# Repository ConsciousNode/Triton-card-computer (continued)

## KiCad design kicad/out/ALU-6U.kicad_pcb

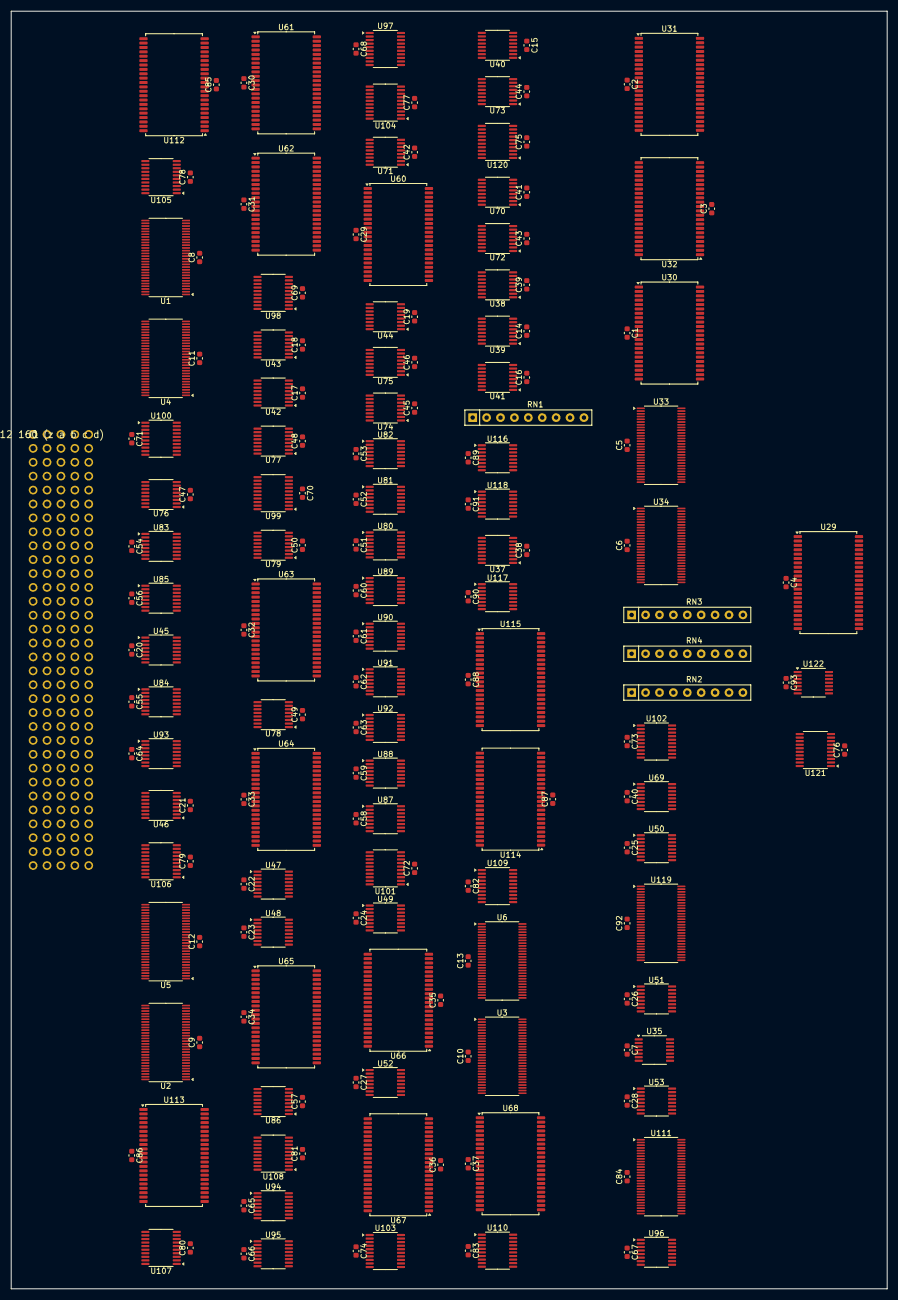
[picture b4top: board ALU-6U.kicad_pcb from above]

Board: 4 copper layers, 160.0 x 233.3 mm, 191 parts (0 on the bottom side), 470 nets, no tracks yet.

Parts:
C1, C2, C3, C4, C5, C6, C7, C8, C9, C10, C11, C12, C13, C14, C15, C16, C17, C18, C19, C20, C21, C22, C23, C24, C25, C26, C27, C28, C29, C30, C31, C32, C33, C34, C35, C36, C37, C38, C39, C40, C41, C42, C43, C44, C45, C46, C47, C48, C49, C50, C51, C52, C53, C54, C55, C56, C57, C58, C59, C60, C61, C62, C63, C64, C65, C66, C67, C68, C69, C70, C71, C72, C73, C74, C75, C76, C77, C78, C79, C80, C81, C82, C83, C84, C85, C86, C87, C88, C89, C90, C91, C92, C93: 100n; C_0603_1608Metric
J1: DIN41612 160 (z a b c d)
RN1, RN2, RN3, RN4: RPACK8; R_Array_SIP9
U1, U2, U3, U4, U5, U6, U33, U34, U111, U119: ALVCH16823; TSSOP-56_6.1x14mm_P0.5mm
U29, U30, U31, U32, U60, U61, U62, U63, U64, U65, U66, U67, U68, U112, U113, U114, U115: IS61WV5128; TSOP-II-44_10.16x18.41mm_P0.8mm
U35: LVC32; TSSOP-14_4.4x5mm_P0.65mm
U37, U39, U40, U69, U116, U117, U118: LVC153; TSSOP-16_4.4x5mm_P0.65mm
U38, U41, U42, U43, U44, U45, U46, U47, U48, U49, U50, U51, U52, U53: LVC157; TSSOP-16_4.4x5mm_P0.65mm
U70, U71, U72, U73, U74, U75, U76, U77, U78, U79, U80, U81, U82, U83, U84, U85, U86, U87, U88, U89, U90, U91, U92, U93, U94, U95, U96: CBTLV3253; TSSOP-16_4.4x5mm_P0.65mm
U97, U98, U99, U100, U101, U102, U103, U120, U121: CBTLV3245; TSSOP-20_4.4x6.5mm_P0.65mm
U104, U105, U106, U107, U108, U109, U110: LVC245; TSSOP-20_4.4x6.5mm_P0.65mm
U122: LVC04; TSSOP-14_4.4x5mm_P0.65mm

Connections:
+3V3: C1.1, C2.1, C3.1, C4.1, C5.1, C6.1, C7.1, C8.1, C9.1, C10.1, C11.1, C12.1, C13.1, C14.1, C15.1, C16.1, C17.1, C18.1, C19.1, C20.1, C21.1, C22.1, C23.1, C24.1, C25.1, C26.1, C27.1, C28.1, C29.1, C30.1, C31.1, C32.1, C33.1, C34.1, C35.1, C36.1, C37.1, C38.1, C39.1, C40.1, C41.1, C42.1, C43.1, C44.1, C45.1, C46.1, C47.1, C48.1, C49.1, C50.1, C51.1, C52.1, C53.1, C54.1, C55.1, C56.1, C57.1, C58.1, C59.1, C60.1, C61.1, C62.1, C63.1, C64.1, C65.1, C66.1, C67.1, C68.1, C69.1, C70.1, C71.1, C72.1, C73.1, C74.1, C75.1, C76.1, C77.1, C78.1, C79.1, C80.1, C81.1, C82.1, C83.1, C84.1, C85.1, C86.1, C87.1, C88.1, C89.1, C90.1, C91.1, C92.1, C93.1, J1.z2, J1.z4, J1.z6, J1.z10, J1.z12, J1.z14, J1.z18, J1.z20, J1.z22, J1.z26, J1.z28, J1.z30, RN1.1, RN2.1, RN3.1, RN4.1, U1.1, U1.7, U1.22, U1.28, U1.35, U1.50, U2.1, U2.7, U2.22, U2.28, U2.35, U2.50, U3.1, U3.7, U3.22, U3.28, U3.35, U3.50, U4.1, U4.7, U4.22, U4.28, U4.35, U4.50, U5.1, U5.7, U5.22, U5.28, U5.35, U5.50, U6.1, U6.7, U6.22, U6.28, U6.35, U6.50, U29.11, U29.15, U29.33, U30.11, U30.15, U30.33, U31.11, U31.15, U31.33, U32.11, U32.15, U32.33, U33.1, U33.7, U33.22, U33.28, U33.35, U33.50, U34.1, U34.7, U34.22, U34.28, U34.35, U34.50, U35.14, U37.16, U38.16, U39.4, U39.16, U40.5, U40.15, U40.16, U41.3, U41.6, U41.13, U41.16, U42.16, U43.16, U44.16, U45.16, U46.16, U47.16, U48.16, U49.16, U50.16, U51.16, U52.16, U53.16, U60.11, U60.15, U60.33, U61.11, U61.15, U61.33, U62.11, U62.15, U62.33, U63.11, U63.15, U63.33, U64.11, U64.15, U64.33, U65.11, U65.15, U65.33, U66.11, U66.15, U66.33, U67.11, U67.15, U67.33, U68.11, U68.15, U68.33, U69.16, U70.16, U71.16, U72.16, U73.16, U74.16, U75.16, U76.16, U77.16, U78.16, U79.16, U80.16, U81.16, U82.16, U83.16, U84.16, U85.16, U86.16, U87.16, U88.16, U89.16, U90.16, U91.16, U92.16, U93.16, U94.16, U95.16, U96.16, U97.20, U98.20, U99.20, U100.20, U101.20, U102.20, U103.20, U104.1, U104.20, U105.1, U105.20, U106.1, U106.20, U107.1, U107.20, U108.1, U108.20, U109.1, U109.20, U110.1, U110.20, U111.1, U111.7, U111.22, U111.27, U111.28, U111.30, U111.35, U111.50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
+5V: J1.z8, J1.z16, J1.z24, J1.z32
/A_LD: U1.30, U1.55, U2.30, U2.55, U3.30, U3.55, U35.3
/B_LD: U4.30, U4.55, U5.30, U5.55, U6.30, U6.55, U35.6
/FL_LD: U35.8, U119.55
A0+: U1.3, U38.3, U60.3
A0-: U1.5, U38.6, U60.4
A1+: U1.6, U60.5
A1-: U1.8, U60.6
A2+: U1.9, U60.7
A2-: U1.10, U60.16
A3+: U1.12, U61.3
A3-: U1.13, U61.4
A4+: U1.14, U61.5
A4-: U1.15, U61.6
A5+: U1.16, U61.7
A5-: U1.17, U61.16
A6+: U1.19, U62.3
A6-: U1.20, U62.4
A7+: U1.21, U62.5
A7-: U1.23, U62.6
A8+: U1.24, U62.7
A8-: U1.26, U62.16
A9+: U2.3, U63.3
A9-: U2.5, U63.4
A10+: U2.6, U63.5
A10-: U2.8, U63.6
A11+: U2.9, U63.7
A11-: U2.10, U63.16
A12+: U2.12, U64.3
A12-: U2.13, U64.4
A13+: U2.14, U64.5
A13-: U2.15, U64.6
A14+: U2.16, U64.7
A14-: U2.17, U64.16
A15+: U2.19, U65.3
A15-: U2.20, U65.4
A16+: U2.21, U65.5
A16-: U2.23, U65.6
A17+: U2.24, U65.7
A17-: U2.26, U65.16
A18+: U3.3, U66.3
A18-: U3.5, U66.4
A19+: U3.6, U66.5
A19-: U3.8, U66.6
A20+: U3.9, U66.7
A20-: U3.10, U66.16
A21+: U3.12, U67.3
A21-: U3.13, U67.4
A22+: U3.14, U67.5
A22-: U3.15, U67.6
A23+: U3.16, U67.7
A23-: U3.17, U67.16
A24+: U3.19, U68.3
A24-: U3.20, U68.4
A25+: U3.21, U68.5
A25-: U3.23, U68.6
A26+: U3.24, U68.7
A26-: U3.26, U68.16
ABORT: J1.c15, U35.2, U35.5, U35.10, U111.55
B0+: U4.3, U42.3, U43.10, U45.3, U46.10, U48.3, U49.10, U51.3, U52.10, U60.17
B0-: U4.5, U42.6, U43.13, U45.6, U46.13, U48.6, U49.13, U51.6, U52.13, U60.18
B1+: U4.6, U42.10, U44.3, U45.10, U47.3, U48.10, U50.3, U51.10, U53.3, U60.19
B1-: U4.8, U42.13, U44.6, U45.13, U47.6, U48.13, U50.6, U51.13, U53.6, U60.20
B2+: U4.9, U43.3, U44.10, U46.3, U47.10, U49.3, U50.10, U52.3, U53.10, U60.26
B2-: U4.10, U43.6, U44.13, U46.6, U47.13, U49.6, U50.13, U52.6, U53.13, U60.27
B3+: U4.12, U42.2
B3-: U4.13, U42.5
B4+: U4.14, U42.11
B4-: U4.15, U42.14
B5+: U4.16, U43.2
B5-: U4.17, U43.5
B6+: U4.19, U43.11
B6-: U4.20, U43.14
B7+: U4.21, U44.2
B7-: U4.23, U44.5
B8+: U4.24, U44.11
B8-: U4.26, U44.14
B9+: U5.3, U45.2
B9-: U5.5, U45.5
B10+: U5.6, U45.11
B10-: U5.8, U45.14
B11+: U5.9, U46.2
B11-: U5.10, U46.5
B12+: U5.12, U46.11
B12-: U5.13, U46.14
B13+: U5.14, U47.2
B13-: U5.15, U47.5
B14+: U5.16, U47.11
B14-: U5.17, U47.14
B15+: U5.19, U48.2
B15-: U5.20, U48.5
B16+: U5.21, U48.11
B16-: U5.23, U48.14
B17+: U5.24, U49.2
B17-: U5.26, U49.5
B18+: U6.3, U49.11
B18-: U6.5, U49.14
B19+: U6.6, U50.2
B19-: U6.8, U50.5
B20+: U6.9, U50.11
B20-: U6.10, U50.14
B21+: U6.12, U51.2
B21-: U6.13, U51.5
B22+: U6.14, U51.11
B22-: U6.15, U51.14
B23+: U6.16, U52.2
B23-: U6.17, U52.5
B24+: U6.19, U52.11
B24-: U6.20, U52.14
B25+: U6.21, U53.2
B25-: U6.23, U53.5
B26+: U6.24, U35.12, U53.11
B26-: U6.26, U35.13, U53.14
BS3+: U42.4, U61.17
BS3-: U42.7, U61.18
BS4+: U42.9, U61.19
BS4-: U42.12, U61.20
BS5+: U43.4, U61.26
BS5-: U43.7, U61.27
BS6+: U43.9, U62.17
BS6-: U43.12, U62.18
BS7+: U44.4, U62.19
BS7-: U44.7, U62.20
BS8+: U44.9, U62.26
BS8-: U44.12, U62.27
BS9+: U45.4, U63.17
BS9-: U45.7, U63.18
BS10+: U45.9, U63.19
BS10-: U45.12, U63.20
BS11+: U46.4, U63.26
BS11-: U46.7, U63.27
BS12+: U46.9, U64.17
BS12-: U46.12, U64.18
BS13+: U47.4, U64.19
BS13-: U47.7, U64.20
BS14+: U47.9, U64.26
BS14-: U47.12, U64.27
BS15+: U48.4, U65.17
BS15-: U48.7, U65.18
BS16+: U48.9, U65.19
BS16-: U48.12, U65.20
BS17+: U49.4, U65.26
BS17-: U49.7, U65.27
BS18+: U49.9, U66.17
BS18-: U49.12, U66.18
BS19+: U50.4, U66.19
BS19-: U50.7, U66.20
BS20+: U50.9, U66.26
BS20-: U50.12, U66.27
BS21+: U51.4, U67.17
BS21-: U51.7, U67.18
BS22+: U51.9, U67.19
BS22-: U51.12, U67.20
BS23+: U52.4, U67.26
BS23-: U52.7, U67.27
BS24+: U52.9, U68.17
BS24-: U52.12, U68.18
BS25+: U53.4, U68.19
BS25-: U53.7, U68.20
BS26+: U53.9, U68.26
BS26-: U53.12, U68.27
BTOPNZ: J1.c31, U35.11
C0+: U39.7, U60.28
C0-: U39.9, U60.29
C1+: U60.35, U61.28
C1-: U60.36, U61.29
C2+: U61.35, U62.28
C2-: U61.36, U62.29
C3+: U62.35, U63.28
C3-: U62.36, U63.29
C4+: U63.35, U64.28
C4-: U63.36, U64.29
C5+: U64.35, U65.28
C5-: U64.36, U65.29
C6+: U65.35, U66.28
C6-: U65.36, U66.29
C7+: U66.35, U67.28
C7-: U66.36, U67.29
C8+: U67.35, U68.28
C8-: U67.36, U68.29
C9+: U68.35, U69.5, U115.29
C9-: U68.36, U69.11, U115.30
CF+: J1.c27, U39.5, U119.6, U119.40
CF-: J1.c28, U39.11, U119.8, U119.38
CLK: J1.c10, U1.29, U1.56, U2.29, U2.56, U3.29, U3.56, U4.29, U4.56, U5.29, U5.56, U6.29, U6.56, U33.29, U33.56, U34.29, U34.56, U111.29, U111.56, U119.29, U119.56
CSD0: U30.9, U33.54
CSD1: U30.10, U33.52
CSD2: U30.13, U33.51
CSD3: U30.14, U33.49
CSD4: U30.31, U33.48
CSD5: U30.32, U33.47
CSD6: U30.35, U33.45
CSD7: U30.36, U33.44
CSD8: U31.9, U33.43
CSD9: U31.10, U33.42
CSD10: U31.13, U33.41
CSD11: U31.14, U33.40
CSD12: U31.31, U33.38
CSD13: U31.32, U33.37
CSD14: U31.35, U33.36
CSD15: U31.36, U33.34
CSD16: U32.9, U33.33
CSD17: U32.10, U33.31
CSD18: U32.13, U34.54
CSD19: U32.14, U34.52
CSD20: U32.31, U34.51
CSD21: U32.32, U34.49
CSD22: U32.35, U34.48
CSD23: U32.36, U34.47
CSD24: U29.9, U34.45
CSD25: U29.10, U34.44
CSD26: U29.13, U34.43
CSD27: U29.14, U34.42
CSD28: U29.31, U34.41
CSD29: U29.32, U34.40
CSD30: U29.35, U34.38
CSD31: U29.36, U34.37
CW_/A_CE: RN1.2, U33.3, U35.1
CW_/BUSOE: RN3.7, U34.8, U104.19, U105.19, U106.19, U107.19, U108.19, U109.19, U110.19
CW_/B_CE: RN1.3, U33.5, U35.4
CW_/ESRV: RN4.8, U34.19, U120.19, U121.19
CW_/FL_CE: RN3.8, U34.9, U35.9
CW_/L9OE: RN2.8, U33.21, U97.19, U98.19, U99.19, U100.19, U101.19, U102.19, U103.19
CW_/SHOE: RN2.7, U33.20, U75.1, U75.15, U76.1, U76.15, U77.1, U77.15, U78.1, U78.15, U79.1, U79.15, U80.1, U80.15, U81.1, U81.15, U82.1, U82.15, U83.1, U83.15, U84.1, U84.15, U85.1, U85.15, U86.1, U86.15, U87.1, U87.15, U88.1, U88.15, U89.1, U89.15, U90.1, U90.15, U91.1, U91.15, U92.1, U92.15, U93.1, U93.15, U94.1, U94.15, U95.1, U95.15, U96.1, U96.15
CW_/SHOE_LO: RN4.7, U34.17, U70.1, U70.15, U71.1, U71.15, U72.1, U72.15, U73.1, U73.15, U74.1, U74.15
CW_/SH_CE: RN3.9, U34.10, U119.30
CW_/STR: RN4.9, U34.20, U122.1
CW_BCAST: RN2.4, U33.16, U42.1, U43.1, U44.1, U45.1, U46.1, U47.1, U48.1, U49.1, U50.1, U51.1, U52.1, U53.1
CW_CIN0: RN2.2, U33.14, U39.14
CW_CIN1: RN2.3, U33.15, U39.2
CW_FILL0: RN2.9, U33.23, U69.14
CW_FILL1: RN3.2, U33.24, U69.2
CW_FN0: RN1.4, U33.6, U41.2, U60.30, U61.30, U62.30
CW_FN1: RN1.5, U33.8, U41.5, U60.38, U61.38, U62.38
CW_FN2: RN1.6, U33.9, U41.11, U60.39, U61.39, U62.39
CW_FN3: RN1.7, U33.10, U41.14, U60.40, U61.40, U62.40
CW_FOP0: RN4.4, U34.14, U115.3
CW_FOP1: RN4.5, U34.15, U115.4
CW_FOP2: RN4.6, U34.16, U115.5
CW_FSEL0: RN4.2, U34.12, U116.14, U117.14, U118.14
CW_FSEL1: RN4.3, U34.13, U116.2, U117.2, U118.2
CW_LDQT: RN3.5, U34.5, U38.1
CW_LINK0: RN3.3, U33.26, U37.14
CW_LINK1: RN3.4, U34.3, U37.2
CW_NEG0: RN1.8, U33.12, U40.14
CW_NEG1: RN1.9, U33.13, U40.2
CW_SHS0: RN2.5, U33.17, U70.14, U71.14, U72.14, U73.14, U74.14, U75.14, U76.14, U77.14, U78.14, U79.14, U80.14, U81.14, U82.14, U83.14, U84.14, U85.14, U86.14, U87.14, U88.14, U89.14, U90.14, U91.14, U92.14, U93.14, U94.14, U95.14, U96.14
CW_SHS1: RN2.6, U33.19, U70.2, U71.2, U72.2, U73.2, U74.2, U75.2, U76.2, U77.2, U78.2, U79.2, U80.2, U81.2, U82.2, U83.2, U84.2, U85.2, U86.2, U87.2, U88.2, U89.2, U90.2, U91.2, U92.2, U93.2, U94.2, U95.2, U96.2
CW_W9: RN3.6, U34.6, U41.1
D0+: J1.a1, U1.54, U4.54, U104.18, U112.3, U116.4
D0-: J1.a2, U1.52, U4.52, U104.17, U112.4, U116.12
D1+: J1.a3, U1.51, U4.51, U104.16, U112.5, U117.4
D1-: J1.a4, U1.49, U4.49, U104.15, U112.6, U117.12
D2+: J1.a5, U1.48, U4.48, U104.14, U112.7, U118.4
D2-: J1.a6, U1.47, U4.47, U104.13, U112.16, U118.12
D3+: J1.a7, U1.45, U4.45, U104.12, U112.17
D3-: J1.a9, U1.44, U4.44, U104.11, U112.18
D4+: J1.a10, U1.43, U4.43, U105.18, U112.19
D4-: J1.a11, U1.42, U4.42, U105.17, U112.20
D5+: J1.a12, U1.41, U4.41, U105.16, U112.26
D5-: J1.a13, U1.40, U4.40, U105.15, U112.27
D6+: J1.a14, U1.38, U4.38, U105.14, U112.28
D6-: J1.a15, U1.37, U4.37, U105.13, U112.29
D7+: J1.a17, U1.36, U4.36, U105.12, U112.30
D7-: J1.a18, U1.34, U4.34, U105.11, U112.38
D8+: J1.a19, U1.33, U4.33, U106.18, U112.39
D8-: J1.a20, U1.31, U4.31, U106.17, U112.40
D9+: J1.a21, U2.54, U5.54, U106.16, U113.3
D9-: J1.a22, U2.52, U5.52, U106.15, U113.4
D10+: J1.a23, U2.51, U5.51, U106.14, U113.5
D10-: J1.a25, U2.49, U5.49, U106.13, U113.6
D11+: J1.a26, U2.48, U5.48, U106.12, U113.7
D11-: J1.a27, U2.47, U5.47, U106.11, U113.16
D12+: J1.a28, U2.45, U5.45, U107.18, U113.17
D12-: J1.a29, U2.44, U5.44, U107.17, U113.18
D13+: J1.a30, U2.43, U5.43, U107.16, U113.19
D13-: J1.a31, U2.42, U5.42, U107.15, U113.20
D14+: J1.b1, U2.41, U5.41, U107.14, U113.26
D14-: J1.b2, U2.40, U5.40, U107.13, U113.27
D15+: J1.b3, U2.38, U5.38, U107.12, U113.28
D15-: J1.b4, U2.37, U5.37, U107.11, U113.29
D16+: J1.b5, U2.36, U5.36, U108.18, U113.30
D16-: J1.b6, U2.34, U5.34, U108.17, U113.38
D17+: J1.b7, U2.33, U5.33, U108.16, U113.39
D17-: J1.b9, U2.31, U5.31, U108.15, U113.40
D18+: J1.b10, U3.54, U6.54, U108.14, U114.3
D18-: J1.b11, U3.52, U6.52, U108.13, U114.4
D19+: J1.b12, U3.51, U6.51, U108.12, U114.5
D19-: J1.b13, U3.49, U6.49, U108.11, U114.6
D20+: J1.b14, U3.48, U6.48, U109.18, U114.7
D20-: J1.b15, U3.47, U6.47, U109.17, U114.16
D21+: J1.b17, U3.45, U6.45, U109.16, U114.17
D21-: J1.b18, U3.44, U6.44, U109.15, U114.18
D22+: J1.b19, U3.43, U6.43, U109.14, U114.19
D22-: J1.b20, U3.42, U6.42, U109.13, U114.20
D23+: J1.b21, U3.41, U6.41, U109.12, U114.26
D23-: J1.b22, U3.40, U6.40, U109.11, U114.27
D24+: J1.b23, U3.38, U6.38, U110.18, U114.28
D24-: J1.b25, U3.37, U6.37, U110.17, U114.29
D25+: J1.b26, U3.36, U6.36, U110.16, U114.30
D25-: J1.b27, U3.34, U6.34, U110.15, U114.38
D26+: J1.b28, U3.33, U6.33, U110.14, U114.39
D26-: J1.b29, U3.31, U6.31, U110.13, U114.40
FILL+: U69.7, U96.4
FILL-: U69.9, U96.12
FNU0: U41.4, U63.30, U64.30, U65.30, U66.30, U67.30, U68.30
FNU1: U41.7, U63.38, U64.38, U65.38, U66.38, U67.38, U68.38
FNU2: U41.9, U63.39, U64.39, U65.39, U66.39, U67.39, U68.39
FNU3: U41.12, U63.40, U64.40, U65.40, U66.40, U67.40, U68.40
GND: C1.2, C2.2, C3.2, C4.2, C5.2, C6.2, C7.2, C8.2, C9.2, C10.2, C11.2, C12.2, C13.2, C14.2, C15.2, C16.2, C17.2, C18.2, C19.2, C20.2, C21.2, C22.2, C23.2, C24.2, C25.2, C26.2, C27.2, C28.2, C29.2, C30.2, C31.2, C32.2, C33.2, C34.2, C35.2, C36.2, C37.2, C38.2, C39.2, C40.2, C41.2, C42.2, C43.2, C44.2, C45.2, C46.2, C47.2, C48.2, C49.2, C50.2, C51.2, C52.2, C53.2, C54.2, C55.2, C56.2, C57.2, C58.2, C59.2, C60.2, C61.2, C62.2, C63.2, C64.2, C65.2, C66.2, C67.2, C68.2, C69.2, C70.2, C71.2, C72.2, C73.2, C74.2, C75.2, C76.2, C77.2, C78.2, C79.2, C80.2, C81.2, C82.2, C83.2, C84.2, C85.2, C86.2, C87.2, C88.2, C89.2, C90.2, C91.2, C92.2, C93.2, J1.a8, J1.a16, J1.a24, J1.a32, J1.b8, J1.b16, J1.b24, J1.b32, J1.c8, J1.c16, J1.c24, J1.c32, J1.d8, J1.d16, J1.d24, J1.d32, J1.z1, J1.z3, J1.z5, J1.z7, J1.z9, J1.z11, J1.z13, J1.z15, J1.z17, J1.z19, J1.z21, J1.z23, J1.z25, J1.z27, J1.z29, J1.z31, U1.2, U1.4, U1.11, U1.18, U1.25, U1.27, U1.32, U1.39, U1.46, U1.53, U2.2, U2.4, U2.11, U2.18, U2.25, U2.27, U2.32, U2.39, U2.46, U2.53, U3.2, U3.4, U3.11, U3.18, U3.25, U3.27, U3.32, U3.39, U3.46, U3.53, U4.2, U4.4, U4.11, U4.18, U4.25, U4.27, U4.32, U4.39, U4.46, U4.53, U5.2, U5.4, U5.11, U5.18, U5.25, U5.27, U5.32, U5.39, U5.46, U5.53, U6.2, U6.4, U6.11, U6.18, U6.25, U6.27, U6.32, U6.39, U6.46, U6.53, U29.8, U29.12, U29.26, U29.27, U29.28, U29.29, U29.30, U29.34, U29.37, U29.38, U29.39, U29.40, U29.41, U30.8, U30.12, U30.26, U30.27, U30.28, U30.29, U30.30, U30.34, U30.37, U30.38, U30.39, U30.40, U30.41, U31.8, U31.12, U31.26, U31.27, U31.28, U31.29, U31.30, U31.34, U31.37, U31.38, U31.39, U31.40, U31.41, U32.8, U32.12, U32.26, U32.27, U32.28, U32.29, U32.30, U32.34, U32.37, U32.38, U32.39, U32.40, U32.41, U33.4, U33.11, U33.18, U33.25, U33.30, U33.32, U33.39, U33.46, U33.53, U33.55, U34.4, U34.11, U34.18, U34.25, U34.30, U34.31, U34.32, U34.33, U34.34, U34.36, U34.39, U34.46, U34.53, U34.55, U35.7, U37.1, U37.3, U37.8, U37.13, U37.15, U38.8, U38.10, U38.11, U38.13, U38.14, U38.15, U39.1, U39.6, U39.8, U39.10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
IE: J1.d26, U121.2
LINK+: U37.6, U39.3, U69.4, U111.3
LINK-: U37.10, U39.13, U69.12, U111.5
LN+: U37.7, U111.54, U115.38
LN-: U37.9, U111.52, U115.39
NCF+: U117.7, U119.51
NCF-: U117.9, U119.49
NEG: U40.7, U60.41, U61.41, U62.41, U63.41, U64.41, U65.41, U66.41, U67.41, U68.41
NOF+: U118.7, U119.48
NOF-: U118.9, U119.47
NSF+: U116.7, U119.54
NSF-: U116.9, U119.52
OF+: U115.16, U119.9, U119.37
OF-: U115.17, U119.10, U119.36
PRIV: J1.d25, U120.8
QN+: U38.4, U111.51
QN-: U38.7, U111.49
QT+: J1.c29, U38.2, U111.6
QT-: J1.c30, U38.5, U40.4, U111.8
R0+: U37.5, U60.9, U70.6, U71.5, U99.4
R0-: U37.11, U60.10, U70.10, U71.11, U99.5
R1+: U60.13, U70.4, U71.6, U72.5, U99.6
R1-: U60.14, U70.12, U71.10, U72.11, U99.7
R2+: U60.31, U71.4, U72.6, U73.5, U99.8
R2-: U60.32, U71.12, U72.10, U73.11, U99.9
R3+: U61.9, U72.4, U73.6, U74.5, U100.2
R3-: U61.10, U72.12, U73.10, U74.11, U100.3
R4+: U61.13, U73.4, U74.6, U75.5, U100.4
R4-: U61.14, U73.12, U74.10, U75.11, U100.5
R5+: U61.31, U74.4, U75.6, U76.5, U100.6
R5-: U61.32, U74.12, U75.10, U76.11, U100.7
R6+: U62.9, U75.4, U76.6, U77.5, U100.8
R6-: U62.10, U75.12, U76.10, U77.11, U100.9
R7+: U62.13, U76.4, U77.6, U78.5, U101.2
R7-: U62.14, U76.12, U77.10, U78.11, U101.3
R8+: U62.31, U77.4, U78.6, U79.5, U101.4
R8-: U62.32, U77.12, U78.10, U79.11, U101.5
R9+: U63.9, U70.3, U78.4, U79.6, U80.5, U101.6
R9-: U63.10, U70.13, U78.12, U79.10, U80.11, U101.7
R10+: U63.13, U71.3, U79.4, U80.6, U81.5, U101.8
R10-: U63.14, U71.13, U79.12, U80.10, U81.11, U101.9
R11+: U63.31, U72.3, U80.4, U81.6, U82.5, U102.2
R11-: U63.32, U72.13, U80.12, U81.10, U82.11, U102.3
R12+: U64.9, U73.3, U81.4, U82.6, U83.5, U102.4
R12-: U64.10, U73.13, U81.12, U82.10, U83.11, U102.5
R13+: U64.13, U74.3, U82.4, U83.6, U84.5, U102.6
R13-: U64.14, U74.13, U82.12, U83.10, U84.11, U102.7
R14+: U64.31, U75.3, U83.4, U84.6, U85.5, U102.8
R14-: U64.32, U75.13, U83.12, U84.10, U85.11, U102.9
R15+: U65.9, U76.3, U84.4, U85.6, U86.5, U103.2
R15-: U65.10, U76.13, U84.12, U85.10, U86.11, U103.3
R16+: U65.13, U77.3, U85.4, U86.6, U87.5, U103.4
R16-: U65.14, U77.13, U85.12, U86.10, U87.11, U103.5
R17+: U65.31, U78.3, U86.4, U87.6, U88.5, U103.6
R17-: U65.32, U78.13, U86.12, U87.10, U88.11, U103.7
R18+: U66.9, U79.3, U87.4, U88.6, U89.5
R18-: U66.10, U79.13, U87.12, U88.10, U89.11
R19+: U66.13, U80.3, U88.4, U89.6, U90.5
R19-: U66.14, U80.13, U88.12, U89.10, U90.11
R20+: U66.31, U81.3, U89.4, U90.6, U91.5
R20-: U66.32, U81.13, U89.12, U90.10, U91.11
R21+: U67.9, U82.3, U90.4, U91.6, U92.5
R21-: U67.10, U82.13, U90.12, U91.10, U92.11
R22+: U67.13, U83.3, U91.4, U92.6, U93.5
R22-: U67.14, U83.13, U91.12, U92.10, U93.11
R23+: U67.31, U84.3, U92.4, U93.6, U94.5
R23-: U67.32, U84.13, U92.12, U93.10, U94.11
R24+: U68.9, U85.3, U93.4, U94.6, U95.5
R24-: U68.10, U85.13, U93.12, U94.10, U95.11
R25+: U68.13, U86.3, U94.4, U95.6, U96.5
R25-: U68.14, U86.13, U94.12, U95.10, U96.11
R26+: U37.4, U68.31, U87.3, U95.4, U96.6
R26-: U37.12, U68.32, U87.13, U95.12, U96.10
RESET: J1.c12, U33.2, U33.27, U34.2, U34.27
S0+: U70.7, U97.18, U104.2, U120.18
S0-: U70.9, U97.17, U104.3, U120.17
S1+: U71.7, U97.16, U104.4, U120.16
S1-: U71.9, U97.15, U104.5, U120.15
S2+: U72.7, U97.14, U104.6, U120.14
S2-: U72.9, U97.13, U104.7, U120.13
S3+: U73.7, U97.12, U104.8, U120.12
S3-: U73.9, U97.11, U104.9, U120.11
S4+: U74.7, U98.18, U105.2, U121.18
S4-: U74.9, U98.17, U105.3, U121.17
S5+: U75.7, U98.16, U105.4
S5-: U75.9, U98.15, U105.5
S6+: U76.7, U98.14, U105.6
S6-: U76.9, U98.13, U105.7
S7+: U77.7, U98.12, U105.8
S7-: U77.9, U98.11, U105.9
S8+: U78.7, U99.18, U106.2
S8-: U78.9, U99.17, U106.3
S9+: U79.7, U99.16, U106.4
S9-: U79.9, U99.15, U106.5
S10+: U80.7, U99.14, U106.6
S10-: U80.9, U99.13, U106.7
S11+: U81.7, U99.12, U106.8
S11-: U81.9, U99.11, U106.9
S12+: U82.7, U100.18, U107.2
S12-: U82.9, U100.17, U107.3
S13+: U83.7, U100.16, U107.4
S13-: U83.9, U100.15, U107.5
S14+: U84.7, U100.14, U107.6
S14-: U84.9, U100.13, U107.7
S15+: U85.7, U100.12, U107.8
S15-: U85.9, U100.11, U107.9
S16+: U86.7, U101.18, U108.2
S16-: U86.9, U101.17, U108.3
S17+: U87.7, U101.16, U108.4
S17-: U87.9, U101.15, U108.5
S18+: U88.7, U101.14, U108.6
S18-: U88.9, U101.13, U108.7
S19+: U89.7, U101.12, U108.8
S19-: U89.9, U101.11, U108.9
S20+: U90.7, U102.18, U109.2
S20-: U90.9, U102.17, U109.3
S21+: U91.7, U102.16, U109.4
S21-: U91.9, U102.15, U109.5
S22+: U92.7, U102.14, U109.6
S22-: U92.9, U102.13, U109.7
S23+: U93.7, U102.12, U109.8
S23-: U93.9, U102.11, U109.9
S24+: U94.7, U103.18, U110.2
S24-: U94.9, U103.17, U110.3
S25+: U95.7, U103.16, U110.4
S25-: U95.9, U103.15, U110.5
S26+: U96.7, U103.14, U110.6
S26-: U96.9, U103.13, U110.7
SCF+: U117.5, U119.17, U120.4
SCF-: U117.11, U119.19, U120.5
SF+: J1.c25, U115.6, U119.3, U119.42
SF-: J1.c26, U115.7, U119.5, U119.41
SOF+: U118.5, U119.20, U120.6
SOF-: U118.11, U119.21, U120.7
SSF+: U116.5, U119.15, U120.2
SSF-: U116.11, U119.16, U120.3
STRETCH: J1.c14, U122.2
TCF+: U115.13, U117.6
TCF-: U115.14, U117.10
TOF+: U115.31, U118.6
TOF-: U115.32, U118.10
TS0+: U112.9, U115.18
TS0-: U112.10, U115.19
TS1+: U113.9, U115.20
TS1-: U113.10, U115.26
TS2+: U114.9, U115.27
TS2-: U114.10, U115.28
TSF+: U115.9, U116.6
TSF-: U115.10, U116.10
UA0: J1.b30, U29.3, U30.3, U31.3, U32.3
UA1: J1.b31, U29.4, U30.4, U31.4, U32.4
UA2: J1.c1, U29.5, U30.5, U31.5, U32.5
UA3: J1.c2, U29.6, U30.6, U31.6, U32.6
UA4: J1.c3, U29.7, U30.7, U31.7, U32.7
UA5: J1.c4, U29.16, U30.16, U31.16, U32.16
UA6: J1.c5, U29.17, U30.17, U31.17, U32.17
UA7: J1.c6, U29.18, U30.18, U31.18, U32.18
UA8: J1.c7, U29.19, U30.19, U31.19, U32.19
UA9: J1.c9, U29.20, U30.20, U31.20, U32.20

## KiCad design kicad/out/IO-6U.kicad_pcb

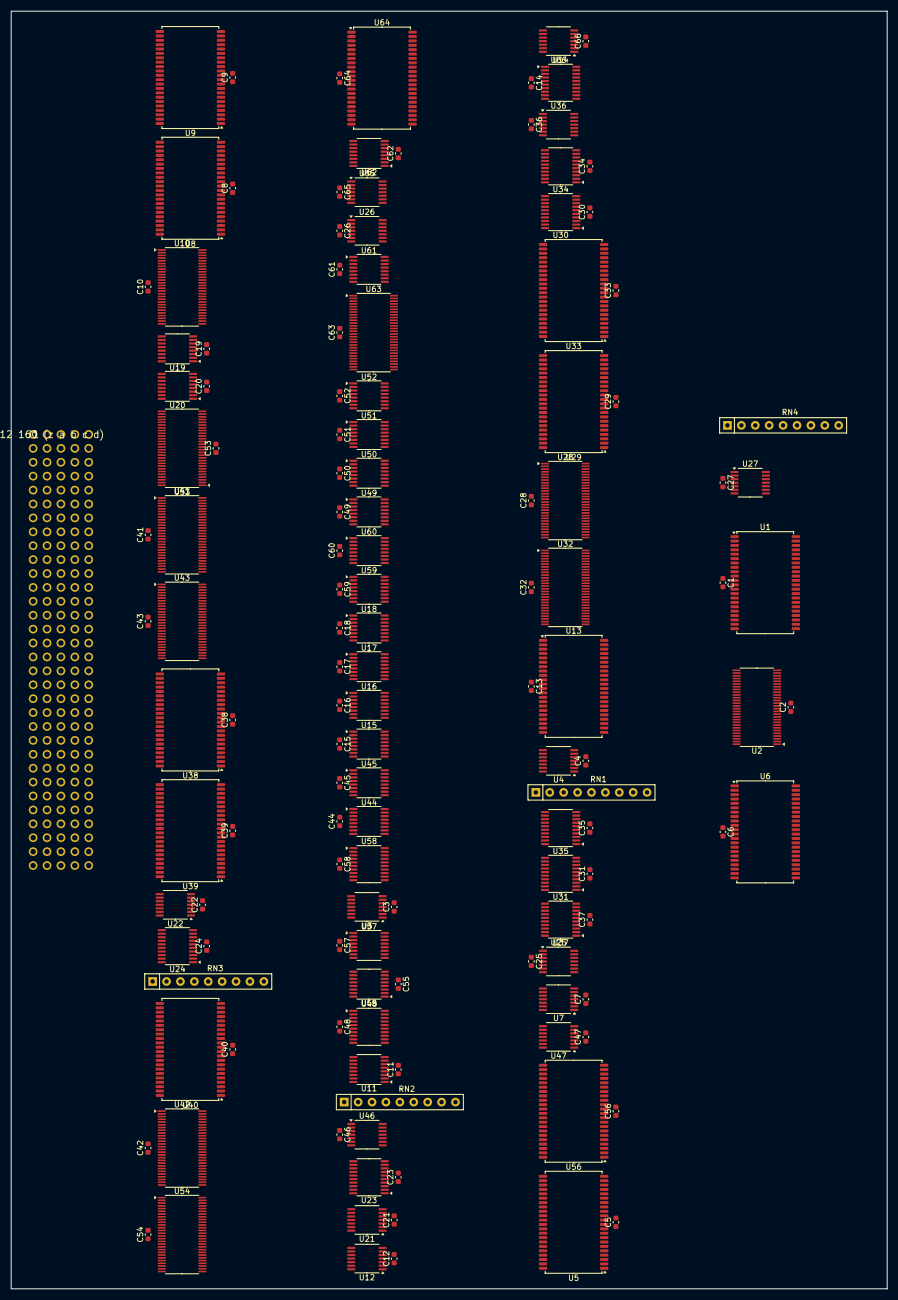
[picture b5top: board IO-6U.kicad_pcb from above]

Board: 4 copper layers, 160.0 x 233.3 mm, 137 parts (0 on the bottom side), 346 nets, no tracks yet.

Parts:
C1, C2, C3, C4, C5, C6, C7, C8, C9, C10, C11, C12, C13, C14, C15, C16, C17, C18, C19, C20, C21, C22, C23, C24, C25, C26, C27, C28, C29, C30, C31, C32, C33, C34, C35, C36, C37, C38, C39, C40, C41, C42, C43, C44, C45, C46, C47, C48, C49, C50, C51, C52, C53, C54, C55, C56, C57, C58, C59, C60, C61, C62, C63, C64, C65, C66: 100n; C_0603_1608Metric
J1: DIN41612 160 (z a b c d)
RN1, RN2, RN3, RN4: RPACK8; R_Array_SIP9
U1, U5, U6, U13, U29, U33, U38, U39, U40, U56, U64: IS61WV5128; TSOP-II-44_10.16x18.41mm_P0.8mm
U2, U10, U28, U32, U41, U42, U43, U53, U54, U63: ALVCH16823; TSSOP-56_6.1x14mm_P0.5mm
U3: LVC04; TSSOP-14_4.4x5mm_P0.65mm
U4: LVC32; TSSOP-14_4.4x5mm_P0.65mm
U7, U12, U25, U26, U27, U46, U47, U65: LVC74; TSSOP-14_4.4x5mm_P0.65mm
U8, U9: IS61WV20488; TSOP-II-44_10.16x18.41mm_P0.8mm
U11: LVC157; TSSOP-16_4.4x5mm_P0.65mm
U14, U30, U31, U34, U35: LVC574; TSSOP-20_4.4x6.5mm_P0.65mm
U15, U16, U17, U18, U44, U45, U49, U50, U51, U52, U59, U60, U61, U62: LVC161; TSSOP-16_4.4x5mm_P0.65mm
U19, U20: LVC165; TSSOP-16_4.4x5mm_P0.65mm
U21, U22: LV164; TSSOP-14_4.4x5mm_P0.65mm
U23, U24, U37: LVC244; TSSOP-20_4.4x6.5mm_P0.65mm
U36: LVC125; TSSOP-14_4.4x5mm_P0.65mm
U48, U58: LV8154; TSSOP-20_4.4x6.5mm_P0.65mm
U55: LVC138; TSSOP-16_4.4x5mm_P0.65mm
U57: CD4060; TSSOP-16_4.4x5mm_P0.65mm
U66: LVC07; TSSOP-14_4.4x5mm_P0.65mm

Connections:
+3V3: C1.1, C2.1, C3.1, C4.1, C5.1, C6.1, C7.1, C8.1, C9.1, C10.1, C11.1, C12.1, C13.1, C14.1, C15.1, C16.1, C17.1, C18.1, C19.1, C20.1, C21.1, C22.1, C23.1, C24.1, C25.1, C26.1, C27.1, C28.1, C29.1, C30.1, C31.1, C32.1, C33.1, C34.1, C35.1, C36.1, C37.1, C38.1, C39.1, C40.1, C41.1, C42.1, C43.1, C44.1, C45.1, C46.1, C47.1, C48.1, C49.1, C50.1, C51.1, C52.1, C53.1, C54.1, C55.1, C56.1, C57.1, C58.1, C59.1, C60.1, C61.1, C62.1, C63.1, C64.1, C65.1, C66.1, J1.z2, J1.z4, J1.z6, J1.z10, J1.z12, J1.z14, J1.z18, J1.z20, J1.z22, J1.z26, J1.z28, J1.z30, RN1.1, RN2.1, RN3.1, RN4.1, U1.11, U1.15, U1.33, U2.1, U2.7, U2.22, U2.28, U2.35, U2.50, U3.14, U4.14, U5.11, U5.15, U5.33, U6.11, U6.15, U6.33, U7.4, U7.10, U7.14, U8.11, U8.15, U8.33, U9.11, U9.15, U9.33, U10.1, U10.7, U10.22, U10.28, U10.35, U10.50, U11.16, U12.4, U12.10, U12.13, U12.14, U13.11, U13.15, U13.33, U14.20, U15.1, U15.16, U16.1, U16.16, U17.1, U17.16, U18.1, U18.16, U19.16, U20.10, U20.16, U21.9, U21.14, U22.9, U22.14, U23.20, U24.20, U25.1, U25.4, U25.10, U25.13, U25.14, U26.1, U26.4, U26.10, U26.13, U26.14, U27.1, U27.4, U27.10, U27.13, U27.14, U28.7, U28.22, U28.35, U28.50, U29.11, U29.15, U29.33, U30.20, U31.20, U32.7, U32.22, U32.35, U32.50, U33.11, U33.15, U33.33, U34.20, U35.20, U36.10, U36.13, U36.14, U37.20, U38.11, U38.15, U38.33, U39.11, U39.15, U39.33, U40.11, U40.15, U40.33, U41.1, U41.7, U41.22, U41.28, U41.35, U41.50, U42.1, U42.7, U42.22, U42.28, U42.35, U42.50, U43.1, U43.7, U43.22, U43.28, U43.35, U43.50, U44.1, U44.6, U44.7, U44.10, U44.16, U45.1, U45.3, U45.4, U45.7, U45.16, U46.4, U46.10, U46.14, U47.4, U47.10, U47.14, U48.20, U49.16, U50.16, U51.16, U52.16, U53.7, U53.22, U53.35, U53.50, U54.7, U54.22, U54.30, U54.35, U54.50, U55.6, U55.16, U56.11, U56.15, U56.33, U57.16, U58.11, U58.20, U59.1, U59.3, U59.5, U59.7, U59.10, U59.16, U60.1, U60.4, U60.6, U60.7, U60.16, U61.1, U61.4, U61.5, U61.6, U61.7, U61.16, U62.3, U62.16, U63.7, U63.22, U63.30, U63.35, U63.50, U64.11, U64.15, U64.33, U65.1, U65.10, U65.13, U65.14, U66.5, U66.9, U66.11, U66.13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
+5V: J1.z8, J1.z16, J1.z24, J1.z32
/BLD: U59.9, U60.9, U61.9, U64.13
/BOE: U4.3, U41.2, U41.27, U42.2, U42.27, U43.2, U43.27
/CBUSY: U64.10, U66.3
/CEDGE: J1.c13, U5.19, U6.19, U29.39, U33.39, U56.19
/CSTART: U6.13, U62.9, U63.55, U64.29
/G0: U48.3, U55.15
/G1: U48.4, U55.14
/G2: U48.5, U55.13
/G3: U48.6, U55.12
/G4: U55.11, U58.3
/G5: U55.10, U58.4
/G6: U55.9, U58.5
/G7: U55.7, U58.6
/ISEL: U4.2, U7.6
/KB: U4.5, U25.8
/KC: U27.6, U28.54
/KCLR: U28.1, U28.28, U30.16
/KCLRD: U29.14, U30.5
/KRDY: U30.13, U36.1
/KRDYD: U29.35, U30.8
/KSH: U4.6, U28.30, U28.55
/LDANS: U5.13, U41.30, U41.55, U42.30, U42.55, U43.30, U43.55
/MB: U4.10, U26.8
/MC: U27.8, U32.54
/MCLR: U32.1, U32.28, U34.16
/MCLRD: U33.14, U34.5
/MRDY: U34.13, U36.4
/MRDYD: U33.35, U34.8
/MSH: U4.8, U32.30, U32.55
/OE_KD: U5.36, U31.1
/OE_MD: U6.9, U35.1
/OE_RX: U5.35, U23.1, U23.19, U24.1, U24.19
/OE_ST: U6.10, U37.1, U37.19
/OE_T: U55.4, U56.14
/PEPRE: U3.6, U44.9, U45.9
/PE_PER: U49.9, U50.9, U51.9, U52.9, U56.31
/PHLD: U13.31, U15.9, U16.9
/PRELD: U13.32, U17.9, U18.9
/RESET: U3.2, U7.1, U7.13, U12.1, U46.1, U46.13, U47.1, U47.13, U48.11, U49.1, U50.1, U51.1, U52.1, U53.1, U53.28, U54.1, U54.28, U62.1, U63.1, U63.28, U65.4
/SCK: U3.4, U19.2, U20.2
/START: U5.9, U10.30, U10.55, U13.38
/WRPH: U53.30, U56.10
/WRPL: U53.55, U56.9
/WRSEL: U54.55, U56.13
ANS0: RN2.2, U23.18, U31.19, U35.19, U37.18, U38.3, U39.3, U40.3, U48.19, U58.19
ANS1: RN2.3, U23.16, U31.18, U35.18, U37.16, U38.4, U39.4, U40.4, U48.18, U58.18
ANS2: RN2.4, U23.14, U31.17, U35.17, U37.14, U38.5, U39.5, U40.5, U48.17, U58.17
ANS3: RN2.5, U23.12, U31.16, U35.16, U37.12, U38.6, U39.6, U40.6, U48.16, U58.16
ANS4: RN2.6, U23.9, U31.15, U35.15, U37.9, U38.7, U39.7, U40.7, U48.15, U58.15
ANS5: RN2.7, U23.7, U31.14, U35.14, U37.7, U38.16, U39.16, U40.16, U48.14, U58.14
ANS6: RN2.8, U23.5, U31.13, U35.13, U37.5, U38.17, U39.17, U40.17, U48.13, U58.13
ANS7: RN2.9, U23.3, U31.12, U35.12, U37.3, U38.18, U39.18, U40.18, U48.12, U58.12
ANS8: RN3.2, U24.18, U38.19, U39.19, U40.19
ANS9: RN3.3, U24.16, U38.20, U39.20, U40.20
ANS10: RN3.4, U24.14, U38.26, U39.26, U40.26
ANS11: RN3.5, U24.12, U38.27, U39.27, U40.27
ANS12: RN3.6, U24.9, U38.28, U39.28, U40.28
ANS13: RN3.7, U24.7, U38.29, U39.29, U40.29
ANS14: RN3.8, U24.5, U38.30, U39.30, U40.30
ANS15: RN3.9, U24.3, U38.38, U39.38, U40.38
BT0: U38.9, U41.54
BT1: U38.10, U41.52
BT2: U38.13, U41.51
BT3: U38.14, U41.49
BT4: U38.31, U41.48
BT5: U38.32, U41.47
BT6: U38.35, U41.45
BT7: U38.36, U41.44
BT8: U39.9, U41.43
BT9: U39.10, U41.42
BT10: U39.13, U41.41
BT11: U39.14, U41.40
BT12: U39.31, U41.38
BT13: U39.32, U41.37
BT14: U39.35, U41.36
BT15: U39.36, U41.34
BT16: U40.9, U41.33
BT17: U40.10, U41.31
BT18: U40.13, U42.54
BT19: U40.14, U42.52
BT20: U40.31, U42.51
BT21: U40.32, U42.49
BTC: U61.15, U62.7, U64.28
BTC0: U59.15, U60.10
BTC1: U60.15, U61.10
BUSY: U13.28, U14.19
BUSYD: U13.9, U14.2
CB0: U62.14, U64.19
CB1: U62.13, U64.20
CB2: U62.12, U64.26
CB3: U62.11, U64.27
CBUSY: U62.10, U64.14
CLK: J1.c10, U2.29, U2.56
CS: U11.2, U12.5
CS0: U63.3, U64.3
CS1: U63.5, U64.4
CS2: U63.6, U64.5
CS3: U63.8, U64.6
CS4: U63.9, U64.7
CS5: U63.10, U64.16
CS6: U63.12, U64.17
CS7: U63.13, U64.18
CSD: U11.4, U12.2
CSD0: U1.9, U2.54
CSD1: U1.10, U2.52
CSD2: U1.13, U2.51
CW_/BIO: RN1.4, U2.6, U4.1
CW_/IN: RN1.2, U2.3, U5.17, U6.17, U56.17
CW_/OUT: RN1.3, U2.5, U5.18, U6.18, U56.18
D0+: J1.a1, U8.3, U9.3, U41.3
D0-: J1.a2, U8.4, U9.4, U41.5
D1+: J1.a3, U8.5, U9.5, U41.6
D1-: J1.a4, U8.6, U9.6, U41.8
D2+: J1.a5, U8.7, U9.7, U41.9
D2-: J1.a6, U8.16, U9.16, U41.10
D3+: J1.a7, U8.17, U9.17, U41.12
D3-: J1.a9, U8.18, U9.18, U41.13
D4+: J1.a10, U8.19, U9.19, U41.14
D4-: J1.a11, U8.20, U9.20, U41.15
D5+: J1.a12, U8.26, U9.26, U41.16
D5-: J1.a13, U8.27, U9.27, U41.17
D6+: J1.a14, U8.28, U9.28, U41.19
D6-: J1.a15, U8.29, U9.29, U41.20
D7+: J1.a17, U8.30, U9.30, U41.21
D7-: J1.a18, U8.38, U9.38, U41.23
D8+: J1.a19, U8.39, U9.39, U41.24
D8-: J1.a20, U8.40, U9.40, U41.26
D9+: J1.a21, U42.3
D9-: J1.a22, U42.5
D10+: J1.a23, U42.6
D10-: J1.a25, U42.8
D11+: J1.a26, U42.9
D11-: J1.a27, U42.10
D12+: J1.a28, U42.12
D12-: J1.a29, U42.13
D13+: J1.a30, U42.14
D13-: J1.a31, U42.15
D14+: J1.b1, U42.16
D14-: J1.b2, U42.17
D15+: J1.b3, U42.19
D15-: J1.b4, U42.20
D16+: J1.b5, U42.21
D16-: J1.b6, U42.23
D17+: J1.b7, U42.24
D17-: J1.b9, U42.26
D18+: J1.b10, U43.3
D18-: J1.b11, U43.5
D19+: J1.b12, U43.6
D19-: J1.b13, U43.8
D20+: J1.b14, U43.9
D20-: J1.b15, U43.10
D21+: J1.b17, U43.12
D21-: J1.b18, U43.13
D22+: J1.b19, U43.14
D22-: J1.b20, U43.15
D23+: J1.b21, U43.16
D23-: J1.b22, U43.17
D24+: J1.b23, U43.19
D24-: J1.b25, U43.20
D25+: J1.b26, U43.21
D25-: J1.b27, U43.23
D26+: J1.b28, U43.24
D26-: J1.b29, U43.26
FAST: U7.9, U11.5, U13.30
FASTD: U7.12, U11.7
GND: C1.2, C2.2, C3.2, C4.2, C5.2, C6.2, C7.2, C8.2, C9.2, C10.2, C11.2, C12.2, C13.2, C14.2, C15.2, C16.2, C17.2, C18.2, C19.2, C20.2, C21.2, C22.2, C23.2, C24.2, C25.2, C26.2, C27.2, C28.2, C29.2, C30.2, C31.2, C32.2, C33.2, C34.2, C35.2, C36.2, C37.2, C38.2, C39.2, C40.2, C41.2, C42.2, C43.2, C44.2, C45.2, C46.2, C47.2, C48.2, C49.2, C50.2, C51.2, C52.2, C53.2, C54.2, C55.2, C56.2, C57.2, C58.2, C59.2, C60.2, C61.2, C62.2, C63.2, C64.2, C65.2, C66.2, J1.a8, J1.a16, J1.a24, J1.a32, J1.b8, J1.b16, J1.b24, J1.b32, J1.c8, J1.c16, J1.c24, J1.c32, J1.d8, J1.d16, J1.d24, J1.d32, J1.z1, J1.z3, J1.z5, J1.z7, J1.z9, J1.z11, J1.z13, J1.z15, J1.z17, J1.z19, J1.z21, J1.z23, J1.z25, J1.z27, J1.z29, J1.z31, U1.8, U1.12, U1.26, U1.27, U1.28, U1.29, U1.30, U1.34, U1.37, U1.38, U1.39, U1.40, U1.41, U2.4, U2.11, U2.18, U2.25, U2.30, U2.31, U2.32, U2.33, U2.34, U2.36, U2.37, U2.38, U2.39, U2.40, U2.41, U2.42, U2.43, U2.44, U2.45, U2.46, U2.47, U2.48, U2.49, U2.53, U2.55, U3.7, U4.7, U5.8, U5.12, U5.26, U5.27, U5.28, U5.29, U5.30, U5.34, U5.37, U5.38, U5.39, U5.40, U5.41, U6.8, U6.12, U6.26, U6.27, U6.28, U6.29, U6.30, U6.34, U6.37, U6.38, U6.39, U6.40, U6.41, U7.7, U8.8, U8.12, U8.34, U8.37, U9.8, U9.12, U9.34, U9.37, U10.2, U10.4, U10.11, U10.18, U10.25, U10.27, U10.31, U10.32, U10.33, U10.39, U10.46, U10.53, U11.8, U11.10, U11.11, U11.13, U11.14, U11.15, U12.7, U12.11, U12.12, U13.8, U13.12, U13.34, U13.37, U13.41, U14.1, U14.6, U14.7, U14.8, U14.9, U14.10, U15.3, U15.4, U15.5, U15.6, U15.8, U16.3, U16.4, U16.5, U16.6, U16.8, U17.3, U17.4, U17.5, U17.6, U17.8, U18.3, U18.4, U18.5, U18.6, U18.8, U19.8, U19.15, U20.8, U20.15, U21.7, U22.7, U23.10, U24.10, U25.7, U26.7, U27.7, U28.2, U28.4, U28.11, U28.18, U28.25, U28.27, U28.31, U28.32, U28.33, U28.34, U28.36, U28.37, U28.38, U28.39, U28.40, U28.46, U28.53, U29.8, U29.12, U29.34, U29.37, U30.1, U30.9, U30.10, U31.10, U32.2, U32.4, U32.11, U32.18, U32.25, U32.27, U32.31, U32.32, U32.33, U32.34, U32.36, U32.37, U32.38, U32.39, U32.40, U32.46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
IORDY: J1.d4, RN4.2, U66.2, U66.4
IRQ0D: U46.12, U56.32
IRQSET0: J1.d5, U46.9, U56.27
IRQSET1: J1.d6, U29.28, U30.18
IRQSET2: J1.d7, U33.28, U34.18
ISEL: U5.20, U6.20, U7.5
ISELD: U5.14, U7.2
KA: U4.4, U25.5, U25.12
KCAPD: U29.13, U30.4
KCAPQ: U29.29, U30.17, U31.11
KFERR: U29.41, U30.14, U37.8
KFERRD: U29.32, U30.7
KIRQD: U29.10, U30.3
KPERR: U29.40, U30.15, U37.6
KPERRD: U29.31, U30.6
KRDY: U29.27, U30.19, U37.4
KRDYD: U29.9, U30.2
KS0: U28.3, U28.52, U29.3
KS1: U28.5, U28.51, U29.4
KS2: U28.6, U28.49, U29.5, U31.9
KS3: U28.8, U28.48, U29.6, U31.8
KS4: U28.9, U28.47, U29.7, U31.7
KS5: U28.10, U28.45, U29.16, U31.6
KS6: U28.12, U28.44, U29.17, U31.5
KS7: U28.13, U28.43, U29.18, U31.4
KS8: U28.14, U28.42, U29.19, U31.3
KS9: U28.15, U28.41, U29.20, U31.2
KS10: U28.16, U29.26
MA: U4.9, U26.5, U26.12
MCAPD: U33.13, U34.4
MCAPQ: U33.29, U34.17, U35.11
MFERR: U33.41, U34.14, U37.15
MFERRD: U33.32, U34.7
MIRQD: U33.10, U34.3
MPERR: U33.40, U34.15, U37.13
MPERRD: U33.31, U34.6
MRDY: U33.27, U34.19, U37.11
MRDYD: U33.9, U34.2
MS0: U32.3, U32.52, U33.3
MS1: U32.5, U32.51, U33.4
MS2: U32.6, U32.49, U33.5, U35.9
MS3: U32.8, U32.48, U33.6, U35.8
MS4: U32.9, U32.47, U33.7, U35.7
MS5: U32.10, U32.45, U33.16, U35.6
MS6: U32.12, U32.44, U33.17, U35.5
MS7: U32.13, U32.43, U33.18, U35.4
MS8: U32.14, U32.42, U33.19, U35.3
MS9: U32.15, U32.41, U33.20, U35.2
MS10: U32.16, U33.26
N16: U13.29, U14.18
N16D: U13.10, U14.3
PH1: U13.18, U15.13
PH2: U13.19, U15.12
PH3: U13.20, U15.11
PH4: U13.26, U16.14
PH5: U13.27, U16.13
PHCE: U13.14, U15.7, U15.10, U16.7
PHTC: U15.15, U16.10
PORT0: J1.d17, U5.3, U6.3, U8.41, U9.41, U38.39, U39.39, U40.39, U56.3
PORT1: J1.d18, U5.4, U6.4, U8.25, U9.25, U13.39, U38.40, U39.40, U40.40, U56.4
PORT2: J1.d19, U5.5, U6.5, U8.42, U9.42, U38.41, U39.41, U40.41, U56.5
PORT3: J1.d20, U5.6, U6.6, U56.6
PORT4: J1.d21, U5.7, U6.7, U56.7
PORT5: J1.d22, U5.16, U6.16, U56.16
PRE0: U13.3, U17.14
PRE1: U13.4, U17.13
PRE2: U13.5, U17.12
PRE3: U13.6, U17.11
PRE4: U13.7, U18.14
PRE5: U13.16, U18.13
PRECE: U13.35, U17.7, U17.10, U18.7
PRETC: U17.15, U18.10
PTC0: U49.15, U50.10
PTC1: U50.15, U51.10
PTC2: U51.15, U52.10
QL: U19.10, U20.9
RCLKD: U47.12, U56.36
RCLKQ: U47.9, U48.7, U58.7
RDK: U5.31, U29.30
RDM: U5.32, U33.30
READYD: U13.36, U14.5
RESET: J1.c12, U2.2, U2.27, U3.1, U4.13, U13.40, U29.38, U33.38, U56.29
RTC_2HZ: U57.3, U58.1, U58.2
RX0: U21.3, U23.2
RX1: U21.4, U23.4
RX2: U21.5, U23.6
RX3: U21.6, U23.8
RX4: U21.10, U23.11
RX5: U21.11, U23.13
RX6: U21.12, U23.15
RX7: U21.13, U22.1, U22.2, U23.17
RX8: U22.3, U24.2
RX9: U22.4, U24.4
RX10: U22.5, U24.6
RX11: U22.6, U24.8
RX12: U22.10, U24.11
RX13: U22.11, U24.13
RX14: U22.12, U24.15
RX15: U22.13, U24.17
SCK: U3.3, U13.17, U15.14, U21.8, U22.8
SCLK: J1.c11, U7.3, U7.11, U10.29, U10.56, U12.3, U14.11, U15.2, U16.2, U17.2, U18.2, U25.3, U25.11, U26.3, U26.11, U27.3, U27.11, U28.29, U28.56, U30.11, U32.29, U32.56, U34.11, U41.29, U41.56, U42.29, U42.56, U43.29, U43.56, U44.2, U45.2, U46.3, U46.11, U47.3, U47.11, U49.2, U50.2, U51.2, U52.2, U53.29, U53.56, U54.29, U54.56, U59.2, U60.2, U61.2, U62.2, U63.29, U63.56, U65.3, U65.11
SD_MISO: U21.1, U21.2
SEL0: U54.3, U55.1
SEL1: U54.5, U55.2
SEL2: U54.6, U55.3
SH/LD: U14.17, U19.1, U20.1
SHLDD: U13.13, U14.4
SNAPP: U47.5, U56.28
SNAPPD: U47.2, U56.35
SREADY: U14.16, U66.1
TB0: U8.9, U10.54
TB1: U8.10, U10.52
TB2: U8.13, U10.51
TB3: U8.14, U10.49
TB4: U8.31, U10.48
TB5: U8.32, U10.47
TB6: U8.35, U10.45
TB7: U8.36, U10.44
TB8: U9.9, U10.43, U11.3, U53.42, U53.54, U54.54, U63.54
TB9: U9.10, U10.42, U11.6, U53.41, U53.52, U54.52, U63.52
TB10: U9.13, U10.41, U53.40, U53.51, U54.51, U63.51
TB11: U9.14, U10.40, U53.38, U53.49, U54.49, U63.49
TB12: U9.31, U10.38, U53.37, U53.48, U63.48
TB13: U9.32, U10.37, U53.36, U53.47, U63.47
TB14: U9.35, U10.36, U53.34, U53.45, U63.45
TB15: U9.36, U10.34, U53.33, U53.44, U63.44
TC4: U52.15, U56.20
TEN: U49.10, U54.8
TICK: U4.12, U45.15, U46.2, U49.7, U50.7, U51.7, U52.7, U56.26
TICKQ: U46.5, U48.1, U48.2
TPH0: U51.3, U53.15
TPH1: U51.4, U53.16
TPH2: U51.5, U53.17
TPH3: U51.6, U53.19
TPH4: U52.3, U53.20
TPH5: U52.4, U53.21
TPH6: U52.5, U53.23
TPH7: U52.6, U53.24
TPL0: U49.3, U53.3
TPL1: U49.4, U53.5
TPL2: U49.5, U53.6
TPL3: U49.6, U53.8
TPL4: U50.3, U53.9
TPL5: U50.4, U53.10
TPL6: U50.5, U53.12
TPL7: U50.6, U53.13
TPTC: U44.15, U45.10
TRST: U3.5, U4.11
TX0: U10.3, U20.11
TX1: U10.5, U20.12
TX2: U10.6, U20.13
TX3: U10.8, U20.14
TX4: U10.9, U20.3
TX5: U10.10, U20.4
TX6: U10.12, U20.5
TX7: U10.13, U20.6
TX8: U10.14, U19.11
TX9: U10.15, U19.12
TX10: U10.16, U19.13
TX11: U10.17, U19.14
TX12: U10.19, U19.3
TX13: U10.20, U19.4
TX14: U10.21, U19.5
TX15: U10.23, U19.6
TXD_D: U64.9, U65.2
U48_RCOA: U48.8, U48.9
U58_RCOA: U58.8, U58.9
UA0: J1.b30, U1.3
UA1: J1.b31, U1.4
UA2: J1.c1, U1.5
UA3: J1.c2, U1.6
UA4: J1.c3, U1.7
UA5: J1.c4, U1.16
UA6: J1.c5, U1.17
UA7: J1.c6, U1.18
UA8: J1.c7, U1.19
UA9: J1.c9, U1.20
WR41: U5.10, U11.1
